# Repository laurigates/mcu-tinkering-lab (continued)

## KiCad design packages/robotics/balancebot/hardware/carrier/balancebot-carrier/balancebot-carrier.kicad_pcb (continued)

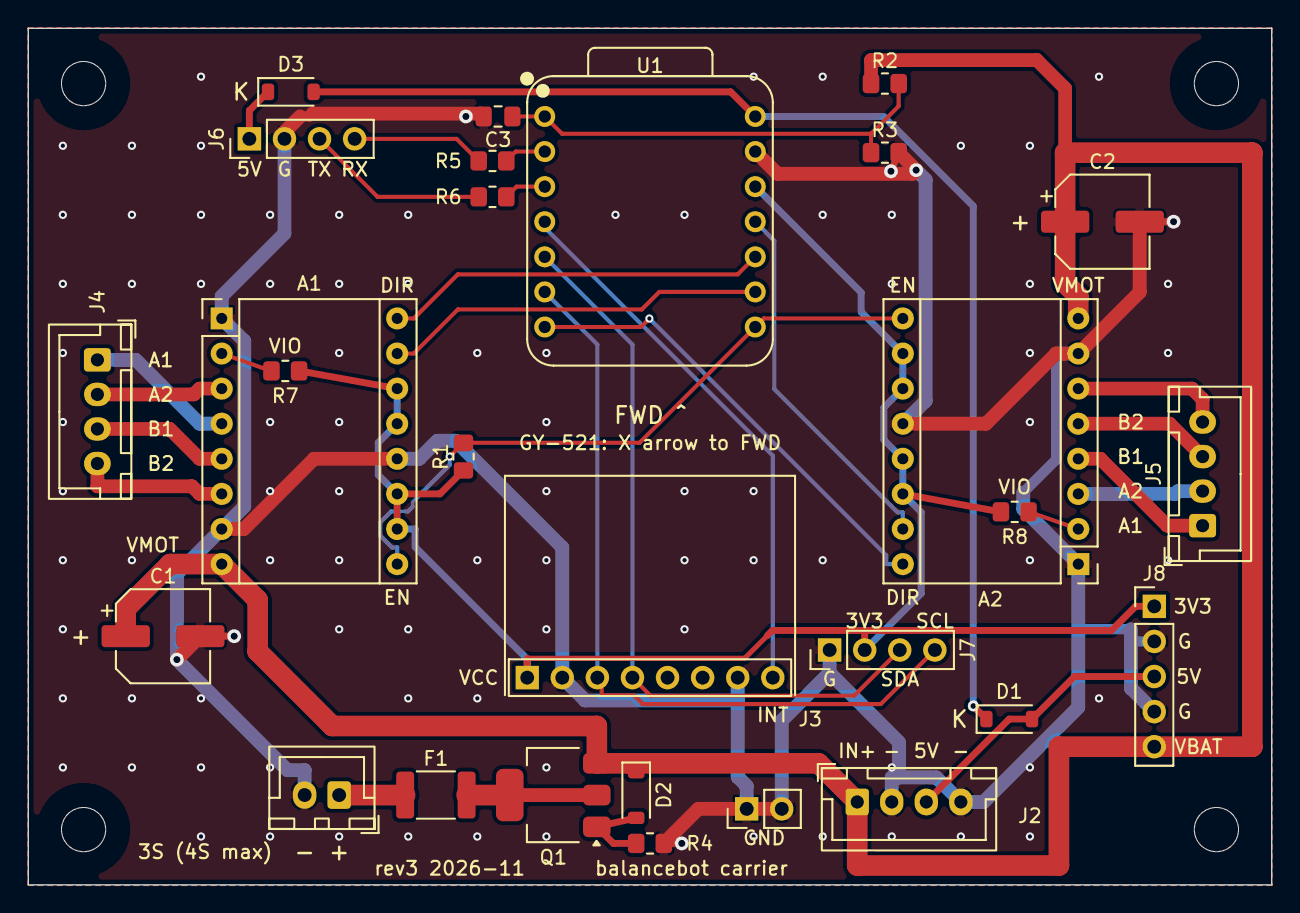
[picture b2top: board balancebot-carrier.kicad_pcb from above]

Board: 2 copper layers, 90.0 x 62.0 mm, 32 parts (0 on the bottom side), 32 nets.

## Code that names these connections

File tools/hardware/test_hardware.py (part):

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        with tempfile.TemporaryDirectory() as tmp:
            h = write(
                Path(tmp) / "a.h",
                "#define A_H\n#define I2C_SDA_PIN GPIO_NUM_5\n",
            )
            self.assertEqual(parse_defines([h]), {"I2C_SDA_PIN": "GPIO_NUM_5"})

    def test_conflicting_redefinition_is_an_error(self):
        # Output would otherwise depend on argument order.
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class RobocarConventionTest(unittest.TestCase):
    def test_only_gpio_num_macros_are_roles(self):
        defines = {
            "I2C_SDA_PIN": "GPIO_NUM_5",
            "I2C_MASTER_FREQ_HZ": "400000",
            "PCA9685_ADDR": "0x40",
            "MOTOR_LEFT_PWM_CHANNEL": "13",
        }
        self.assertEqual(roles_from_defines(defines, "robocar"), {"I2C_SDA_PIN": 5})

    def test_unknown_convention_is_an_error_naming_the_known_ones(self):
        with self.assertRaisesRegex(HardwareError, "balancebot.*robocar"):
            roles_from_defines({}, "gamepad-synth")

    def test_a_bare_integer_is_not_a_robocar_pin_even_with_a_pin_name(self):
        self.assertEqual(roles_from_defines({"PIN_IMU_SDA": "6"}, "robocar"), {})


class BalancebotConventionTest(unittest.TestCase):
    def test_pin_prefixed_bare_integers_are_roles(self):
        defines = {
            "PIN_IMU_SDA": "6",
            "PIN_STATUS_LED": "25",
            "CONTROL_LOOP_HZ": "500",  # a bare integer, but not a pin
            "MPU6050_ADDR": "0x68",
            "SPIN_COUNT": "3",  # PIN_ inside the name, not at its start
            "PIN_ALIAS": "PIN_IMU_SDA",  # not an integer
        }
        self.assertEqual(
            roles_from_defines(defines, "balancebot"),
            {"PIN_IMU_SDA": 6, "PIN_STATUS_LED": 25},
        )

    def test_gpio_num_values_are_not_balancebot_pins(self):
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        self.assertEqual(
            roles_from_defines(defines, "balancebot"),
            {
                "PIN_IMU_SDA": 6,
                "PIN_IMU_SCL": 7,
                "PIN_IMU_INT": 5,
                "PIN_STEP_LEFT": 2,
                "PIN_STEP_RIGHT": 3,
                "PIN_DIR_LEFT": 4,
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                "PIN_STATUS_LED": 25,
                "PIN_BATT_ADC": 29,
                "PIN_BATT_ADC_ENABLE": 19,
                "PIN_PACK_SENSE": 26,
                "PIN_EXP_D1": 27,
                "PIN_EXP_D2": 28,
            },
        )

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        # #722: a pin conflict is a wiring error, so the join reports it
        # rather than leaving it to surface as a router failure. The second
        # role is excused, so the conflict alone can be what fails.
        header = HEADER_H + "#define PIEZO_PIN GPIO_NUM_1\n"
        sidecar = SIDECAR + '\n[[undrawn]]\nrole = "PIEZO_PIN"\nwhy = "test"\n'
        with self.assertRaises(HardwareError) as ctx:
            self.join(self.make(sidecar=sidecar, header=header))
        message = str(ctx.exception)
        self.assertIn("LED_PIN", message)
        self.assertIn("PIEZO_PIN", message)
        self.assertIn("GPIO1", message)

    def test_a_macro_naming_another_role_is_an_alias_not_a_second_role(self):
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
    def test_a_rail_on_a_channel_net_fails(self):
        rail = '\n[[rails]]\nname = "5V"\nfrom = "mcu.5V"\nto = ["{}"]\n'
        for pin, role in (("motor.PWMA", "SPEED_CHANNEL"), ("drv.1", "SPEED_CHANNEL")):
            with (
                self.subTest(pin=pin),
                self.assertRaisesRegex(HardwareError, f"{pin}.*{role}"),
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
    def test_dropping_an_undrawn_entry_from_the_committed_sidecar_fails(self):
        # The completeness gate (#460) holds on the real project, not only on
        # the synthetic one: in the harness view UART0_TX_PIN is excused only by
        # this entry (the carrier wires it to the UART0 tap).
        text = (ROBOCAR / "hardware.toml").read_text(encoding="utf-8")
        entry = re.search(
            r'\[\[undrawn\]\]\nrole = "UART0_TX_PIN"\nbuild = "harness"\n'
            r'why = "[^"\n]*"\n\n?',
            text,
        )
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            (proj / "hardware.toml").write_text(
                text.replace(entry.group(0), ""), encoding="utf-8"
            )
            with self.assertRaisesRegex(HardwareError, "UART0_TX_PIN"):
                join(proj, repo_root=REPO_ROOT)

    def test_moving_the_piezo_onto_the_mux_reset_fails(self):
        # #722's repro: PIEZO_PIN GPIO_NUM_2 -> GPIO_NUM_3, which is now
        # TCA9548A_RST_PIN's pin (#782; it was the ultrasonic trigger's). Every
        # generator used to accept it; the router failed later.
        header = (ROBOCAR / "main/pin_config.h").read_text(encoding="utf-8")
        moved = header.replace(
            "#define PIEZO_PIN GPIO_NUM_2", "#define PIEZO_PIN GPIO_NUM_3"
        )
        self.assertNotEqual(moved, header)
        with tempfile.TemporaryDirectory() as tmp:
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            with self.assertRaises(HardwareError) as ctx:
                join(proj, repo_root=REPO_ROOT)
        message = str(ctx.exception)
        self.assertIn("PIEZO_PIN", message)
        self.assertIn("TCA9548A_RST_PIN", message)
        self.assertIn("GPIO3", message)

    def test_i2s_lands_on_the_amp_via_d8_d9_d10(self):
        nets = {n.role: (n.part, n.pin) for n in self.model.nets}
        self.assertEqual(nets["I2S_BCLK_PIN"], ("amp", "BCLK"))
        self.assertEqual(self.model.pin_for("I2S_BCLK_PIN").name, "D8")
        self.assertEqual(self.model.pin_for("I2S_LRCLK_PIN").name, "D9")
        self.assertEqual(self.model.pin_for("I2S_DIN_PIN").name, "D10")

    def test_the_microphone_is_excused_and_on_no_header_pad(self):
        undrawn = {u.role for u in self.model.undrawn}
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        # Promoted from a doc comment to real macros (#461) so the build guide
        # and WIRING.md stop hand-typing GPIO43/44.
        undrawn = {u.role for u in self.model.undrawn}
        self.assertLessEqual({"UART0_TX_PIN", "UART0_RX_PIN"}, undrawn)
        self.assertEqual(self.model.pin_for("UART0_TX_PIN").name, "D6")
        self.assertEqual(self.model.pin_for("UART0_RX_PIN").name, "D7")

    def rail_of(self) -> dict[tuple[str, str], str]:
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
    def test_the_motor_driver_mapping_agrees_with_pin_config_comments(self):
        # pin_config.h states the PCA9685 -> TB6612FNG mapping in comments
        # (`// -> PWMA`); hardware.toml states it as nets. Pin the two together.
        text = (ROBOCAR / "main/pin_config.h").read_text(encoding="utf-8")
        claimed = dict(re.findall(r"#define (\w+_CHANNEL) \d+\s*// -> (\w+)", text))
        joined = {
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            )
            (proj / "hardware.toml").write_text(sidecar)
            text = self.run_generator(REPO_ROOT, str(proj)).decode()
        self.assertIn("#let PIN_IMU_SDA = 6\n", text)
        self.assertIn("#let PIN_MOTOR_NENABLE = 1\n", text)
        self.assertIn("#let PIN_BATT_ADC_ENABLE = 19\n", text)
        self.assertNotIn("I2C_SDA_PIN", text)
        # Not mounted in the root justfile, so it names the script itself.
        self.assertIn(
            "regenerate with `python3 tools/typst/generate-pin-defs.py ", text
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
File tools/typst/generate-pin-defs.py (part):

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# fmt: off
ROBOCAR_EXTRACT = [
    # ── I2C Bus ──
    ("I2C Bus", "I2C_SDA_PIN",        "I2C_SDA_PIN",        None),
    ("I2C Bus", "I2C_SCL_PIN",        "I2C_SCL_PIN",        None),
    ("I2C Bus", "I2C_MASTER_FREQ_HZ", "I2C_FREQ_HZ",        None),

    # ── TCA9548A Multiplexer ──
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    ("TCA9548A Multiplexer", "I2C_BUS_CHANNEL_MCP23017",  "TCA_CH_MCP23017", None),
    ("TCA9548A Multiplexer", "I2C_BUS_CHANNEL_RANGER_FRONT", "TCA_CH_RANGER_FRONT", None),
    ("TCA9548A Multiplexer", "I2C_BUS_CHANNEL_RANGER_REAR",  "TCA_CH_RANGER_REAR",  None),
    ("TCA9548A Multiplexer", "TCA9548A_RST_PIN",          "MUX_RST_PIN",    None),

    # ── PCA9685 PWM Driver ──
    ("PCA9685 PWM Driver", "PCA9685_ADDR",    "PCA9685_ADDR",    "hex_str"),
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    ("PCA9685 — Motor Channels", "MOTOR_LEFT_PWM_CHANNEL",  "PCA_CH_MOTOR_L_PWM", None),

    # ── Motor Control ──
    ("Motor Control", "MOTOR_STBY_PIN", "MOTOR_STBY_PIN", None),

    # ── MCP23017 GPIO Expander ──
    ("MCP23017 GPIO Expander", "MCP23017_ADDR", "MCP23017_ADDR", "hex_str"),
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    ("RCWL-1601 Rangefinders", "RCWL1601_I2C_ADDR", "RANGER_ADDR", "hex_str"),

    # ── Piezo Buzzer ──
    ("Piezo Buzzer", "PIEZO_PIN", "PIEZO_PIN", None),

    # ── UART0 header pads (nothing wired; the console is USB-Serial-JTAG) ──
    ("UART0 header pads", "UART0_TX_PIN", "UART0_TX_PIN", None),
    ("UART0 header pads", "UART0_RX_PIN", "UART0_RX_PIN", None),

    # ── MAX98357A I2S Audio ──
    ("MAX98357A I2S Audio", "I2S_BCLK_PIN",         "I2S_BCLK_PIN", None),
    ("MAX98357A I2S Audio", "I2S_LRCLK_PIN",        "I2S_LRCLK_PIN", None),
    ("MAX98357A I2S Audio", "I2S_DIN_PIN",          "I2S_DIN_PIN", None),
    ("MAX98357A I2S Audio", "AUDIO_SAMPLE_RATE_HZ", "AUDIO_SAMPLE_RATE_HZ", None),

    # ── Planner cadence (planner_task.h, plan_activity.h) ──
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
BALANCEBOT_EXTRACT = [
    # ── MPU6050 IMU (I2C1) ──
    ("MPU6050 IMU (I2C1)", "PIN_IMU_SDA", "PIN_IMU_SDA", None),
    ("MPU6050 IMU (I2C1)", "PIN_IMU_SCL", "PIN_IMU_SCL", None),
    ("MPU6050 IMU (I2C1)", "PIN_IMU_INT", "PIN_IMU_INT", None),

    # ── DRV8825 Stepper Drivers ──
    ("DRV8825 Stepper Drivers", "PIN_STEP_LEFT",     "PIN_STEP_LEFT",     None),
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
